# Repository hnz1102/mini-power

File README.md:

<div align="center">
  <h1><code>Mini Power for Breadboard</code></h1>
  
</div>

# Mini-Power

Mini-Power is a small, portable DC power supply unit designed to provide a convenient and reliable source of adjustable voltage for your electronic devices and breadboard experiments. Powered from a USB Power Delivery (PD) charger, it supports both Standard Power Range (SPR) and Extended Power Range (EPR) modes, making it perfect for electronics developers, students, and anyone who needs a compact bench power supply.

## Key Features

- **Easy access to the breadboard**: both sides accessible via standard 2.54mm pitch pin headers.
- **USB PD support**: 5V to 28V output using the AP33772S PD Sink Controller.
- **Variable voltage**: 0.1V steps using PPS APDO, with automatic fallback to the nearest Fixed PDO.
- **Real-time display**: SSD1306 128×64 OLED showing output voltage, measured voltage, current, power, WiFi status, and buffer usage.
- **Data logging**: Measurements sent to InfluxDB over WiFi (InfluxDB Line Protocol, HTTPS).
- **Remote syslog**: RFC 5424 over UDP for monitoring and troubleshooting.
- **HTTP web interface**: Real-time graphs (Chart.js), voltage control, and output ON/OFF toggle from any browser on the local network.
- **Three-button interface**: Up / Down / Center push buttons for direct voltage adjustment and output control.
- **NVS persistence**: Last voltage setting is saved to flash and restored on reboot.
- **Safety protections**: OVP, UVP, OCP (in AP33772S hardware) plus software current/power limits and voltage overshoot detection (>110% of setpoint).

## Hardware Components

| Reference | Part | Description |
|---|---|---|
| U103 | ESP32-C3-WROOM-02-N4 | Main microcontroller (RISC-V, built-in WiFi, 4MB flash) |
| U104 | AP33772SDKZ-13-FA01 | USB Power Delivery Sink Controller (SPR + EPR), QFN4040-24 |
| U102 | SSD1306 | Monochrome OLED display (128×64 pixels, I2C) |
| U101 | PCA9306D | Dual bidirectional I2C voltage-level translator (SSOP-8) |
| U105 | NJW1933F1 | Synchronous step-down DC/DC converter for 3.3V supply (SOT-23-6) |
| Q101, Q102 | DMN3008SFG | Dual N-channel MOSFET for output switching (PowerDI3333-8) |
| J101 | USB4105-GF-A | USB Type-C connector (input) |
| J102, J103 | 2×2 pin header | Output terminals (UPPER OUT / LOWER OUT), 2.54mm pitch |
| SW101–SW103 | TS-06104 | Push buttons: Up (GPIO10), Down (GPIO20), Center (GPIO21) |
| R110 | 5mΩ shunt resistor | Current sensing resistor (2512 package) |
| L101 | 22µH | Inductor for DC/DC converter |
| D101 | LED (Blue) | Status indicator |
| D102 | SK36A-LTP | Schottky diode (SMA) |
| FB101 | MH2029-601Y | Ferrite bead for EMI filtering |

Schematic and PCB files are in the `hardware/` directory. The board is designed with [KiCad](https://www.kicad.org/). A PDF export of the schematic is available at [`hardware/schematic.pdf`](hardware/schematic.pdf).

The [ap33772s-driver](https://github.com/hnz1102/ap33772s-driver) crate is used for all USB-PD communication with the AP33772S controller.

## Software Architecture

The firmware is written entirely in Rust using the ESP-IDF framework.

| File | Responsibility |
|---|---|
| `main.rs` | Startup, peripheral init, NVS load/save, main control loop |
| `usbpd.rs` | AP33772S PD driver wrapper (PDO negotiation, custom voltage request, VOUT control) |
| `displayctl.rs` | SSD1306 OLED driver, display thread, PDO list screen |
| `currentlogs.rs` | In-memory ring buffer (up to 127 records) for voltage/current/power/temp data |
| `transfer.rs` | InfluxDB Line Protocol HTTP transfer thread |
| `httpserver.rs` | HTTP server, REST API (`/api/status`, `/api/voltage`, `/api/output`, `/api/pdos`), embedded HTML/JS |
| `keyevent.rs` | GPIO key scanner (10ms polling, 100ms guard time) with long-press detection |
| `wifi.rs` | WiFi connection, RSSI monitoring, automatic reconnect |
| `syslogger.rs` | RFC 5424 UDP syslog, replaces the default ESP console logger |

## How to Use the Unit

### Basic Operation

1. **Connection**: Connect a USB-C PD charger*1 to the input port.
2. **Power On**: The unit negotiates PD profiles and scrolls through the available PDO list on the display.
3. **Main Screen**: After getting a IP address from DHCP server*2, the display shows output voltage, current, power, WiFi RSSI, IP address(last two octets)and buffer usage. 
4. **Voltage Selection**: Press **Up(yellow)** or **Down(blue)** to increase/decrease the target voltage in 0.1V steps.
5. **Output Control**: Press **Center(red)** to toggle output ON/OFF.
6. **Monitoring**: View real-time measurements on the OLED display or open `http://<device-ip>/` in a browser.

**Note** 
*1: When it doesn't connect to the PD charger, the display will show "No PD Power". Click the up/down buttons to show main screen. It only can output 5V.
*2: If it can't connect to WiFi, the display will show the main screen after 30 seconds, but without IP address and RSSI. 

### Button Controls

| Button | GPIO | Function |
|---|---|---|
| Up | GPIO10 | Increase output voltage by 0.1V |
| Down | GPIO20 | Decrease output voltage by 0.1V |
| Center | GPIO21 | Toggle output ON/OFF |

### OLED Display

The SSD1306 128×64 monochrome OLED display is divided into several regions as shown below.

| Area | Content | Detail |
|---|---|---|
| `V:xx.xV` | Measured voltage | Read from AP33772S (updated every 100ms when output ON) |
| `I:xx.xA` | Measured current | Read from AP33772S (updated every 100ms when output ON) |
| `SET:xx.xV` | Target output voltage | Blinks while PD voltage negotiation is in progress |
| `P:xx.xW` / `P:xx.xmW` | Measured power | Auto-range: switches between mW and W (threshold 0.5W / 1.0W) |
| `OUTPUT` / `STOPPED` | Output state | `OUTPUT` shown inverted (white on black) when output is ON |
| IP address | Last two octets of device IP | e.g. `IP:2.142` for `192.168.2.142` |
| Buffer bar | InfluxDB send buffer usage | 60px wide bar; fills left-to-right as records accumulate (max 127) |
| `xxx%` | Buffer usage percentage | Displayed to the right of the buffer bar |
| WiFi icon | WiFi signal strength | 5-level icon (wifi-0 to wifi-4) based on RSSI; animated while connecting |
| `+xx dBm` | RSSI value | Shown below WiFi icon when connected |
| Voltage bar (right edge) | PDO voltage range | Vertical bar showing min–max PD voltage; Variable/PPS range filled, Fixed PDO voltages marked as horizontal lines; current SET voltage shown as a longer line marker |

**Startup sequence:**

1. At boot, the PDO list screen is shown first — all Power Data Objects negotiated with the charger are listed (voltage, current, max power, type). Each page is shown for 3 seconds.
2. After PDO display completes, the main screen appears.
3. Error / warning messages (e.g. `Voltage Overshoot`, `Current OV x.xxxA`) replace the main screen temporarily and auto-dismiss after 3 seconds.

### HTTP Web Interface

When connected to WiFi, open `http://<device-ip>/` (IP shown on OLED display) to access:

- Live voltage, current, and power readings updated every second
- Real-time voltage and current graph (Chart.js)
- PDO table showing all available power profiles from the charger
- Voltage control with +/− buttons (0.1V step)
- Output ON/OFF toggle

### Safety Protections

| Protection | Mechanism |
|---|---|
| Over Voltage Protection (OVP) | AP33772S hardware |
| Under Voltage Protection (UVP) | AP33772S hardware |
| Over Current Protection (OCP) | AP33772S hardware |
| Software current limit | Output disabled if current exceeds `max_current_limit` |
| Software power limit | Output disabled if power exceeds `max_power_limit` |
| Voltage overshoot detection | Output disabled if measured voltage > 110% of setpoint |

## How to Build from Code and Install to the Unit

### Using Ubuntu 22.04 LTS

**1. Install Rust Compiler**

```bash
sudo apt update && sudo apt -y install git python3 python3-pip gcc build-essential \
  curl pkg-config libudev-dev libtinfo5 clang libclang-dev llvm-dev udev libssl-dev python3.10-venv nano
```
```bash
curl --proto '=https' --tlsv1.2 -sSf https://sh.rustup.rs | sh
# Select option 1 (default install)
```
```bash
source "$HOME/.cargo/env"
```

**2. Install toolchain for ESP32-C3**

```bash
cargo install ldproxy
cargo install cargo-binstall
cargo install espup
espup install
espup update
. ./export-esp.sh
cargo binstall cargo-espflash
```

**3. Add UDEV rules**

```bash
sudo sh -c 'echo "SUBSYSTEMS==\"usb\", ATTRS{idVendor}==\"303a\", ATTRS{idProduct}==\"1001\", MODE=\"0666\"" \
  > /etc/udev/rules.d/99-esp32.rules'
sudo udevadm control --reload-rules
sudo udevadm trigger
```

**4. Clone the repository**

```bash
git clone https://github.com/hnz1102/mini-power.git
cd mini-power/code
```

**5. Configure WiFi and InfluxDB**

```bash
cp cfg.toml.samp cfg.toml
nano cfg.toml
```

```toml
[mini-power]
wifi_ssid = "YOUR_WIFI_SSID"
wifi_psk = "YOUR_WIFI_PASSWORD"
influxdb_server = "192.168.x.x:8086"
influxdb_api_key = "<YOUR_API_KEY>"
influxdb_api = "/api/v2/write?org=<ORG>&bucket=LOGGER&precision=ns"
influxdb_measurement = "minipower"
influxdb_tag = "ch"
max_current_limit = "5.2"
max_power_limit = "100.0"
max_temperature = "75"
syslog_server = "192.168.x.x:514"
syslog_enable = "false"
```

**6. Connect the board and verify**

```bash
cargo espflash board-info
# Select /dev/ttyACM0
# Expected: Chip type: esp32c3, Flash size: 4MB
```

**7. Build and flash**

```bash
cargo espflash flash --release --monitor
```

The device boots automatically after flashing. The OLED display will show the PDO list negotiated with the charger, then switch to the main monitoring screen.

## How to Install InfluxDB and Configure the Dashboard

**1. Download and install InfluxDB**

```bash
wget https://dl.influxdata.com/influxdb/releases/influxdb2-2.7.0-amd64.deb
sudo dpkg -i influxdb2-2.7.0-amd64.deb
sudo service influxdb start
```

**2. Initial configuration**

Open `http://<server-ip>:8086`. Click `GET STARTED` and set:

| Term | Value |
|---|---|
| Username | Admin login username |
| Password | Admin login password |
| Initial Organization Name | e.g. `ORG` |
| Initial Bucket Name | `LOGGER` |

**3. Get the API Token**

Copy the Operator API Token shown after setup — you will not see it again. To generate a new token later: `API Tokens` → `GENERATE API TOKEN` → `All access token`.

**4. Import the Dashboard Template**

Click `Dashboard` → `CREATE DASHBOARD` → `Import Dashboard`. Drop the `influxdb/mimi-power.json` file into the import dialog, then click `IMPORT JSON AS DASHBOARD`.

You will see the **Mimi-POWER** dashboard. It contains three time-series graphs:

| Chart | Field | Unit |
|---|---|---|
| Voltage | `voltage` | V |
| Current | `current` | A |
| Power | `power` | W |

All charts query the `LOGGER` bucket, measurement `minipower`, tag `tag = "ch"`.

**5. Start logging**

Enable the output on the Mini-Power unit (Center button or web interface). Measurement data will be sent to InfluxDB and appear on the dashboard in real-time.

## Schematic and PCB Data

The PCB is designed with [KiCad](https://www.kicad.org/). All hardware design files are in the `hardware/` directory.

| File / Directory | Description |
|---|---|
| [`hardware/schematic.pdf`](hardware/schematic.pdf) | Schematic PDF (for viewing without KiCad) |
| `hardware/mini-power.kicad_sch` | KiCad schematic source |
| `hardware/mini-power.kicad_pcb` | KiCad PCB layout |
| `hardware/bom.csv` | Bill of Materials |
| `hardware/production/` | Gerber files for PCB manufacturing (`mini-power.kicad_pcb_gerber.zip`) |

## 3D Printed Enclosure

The enclosure design files are in the `hardware/Container/` directory.

| File | Description |
|---|---|
| `body.3mf` | Main enclosure body |
| `upper.3mf` | Top cover |
| `button.3mf` | Button cap for the three push switches |
| `mini-power.f3d` | Fusion 360 source file |

All parts are designed for FDM 3D printing. Print `body.3mf`, `upper.3mf`, and three copies of `button.3mf`.

## License

This source code is licensed under MIT. Other Hardware Schematic documents are licensed under CC-BY-SA V4.0.

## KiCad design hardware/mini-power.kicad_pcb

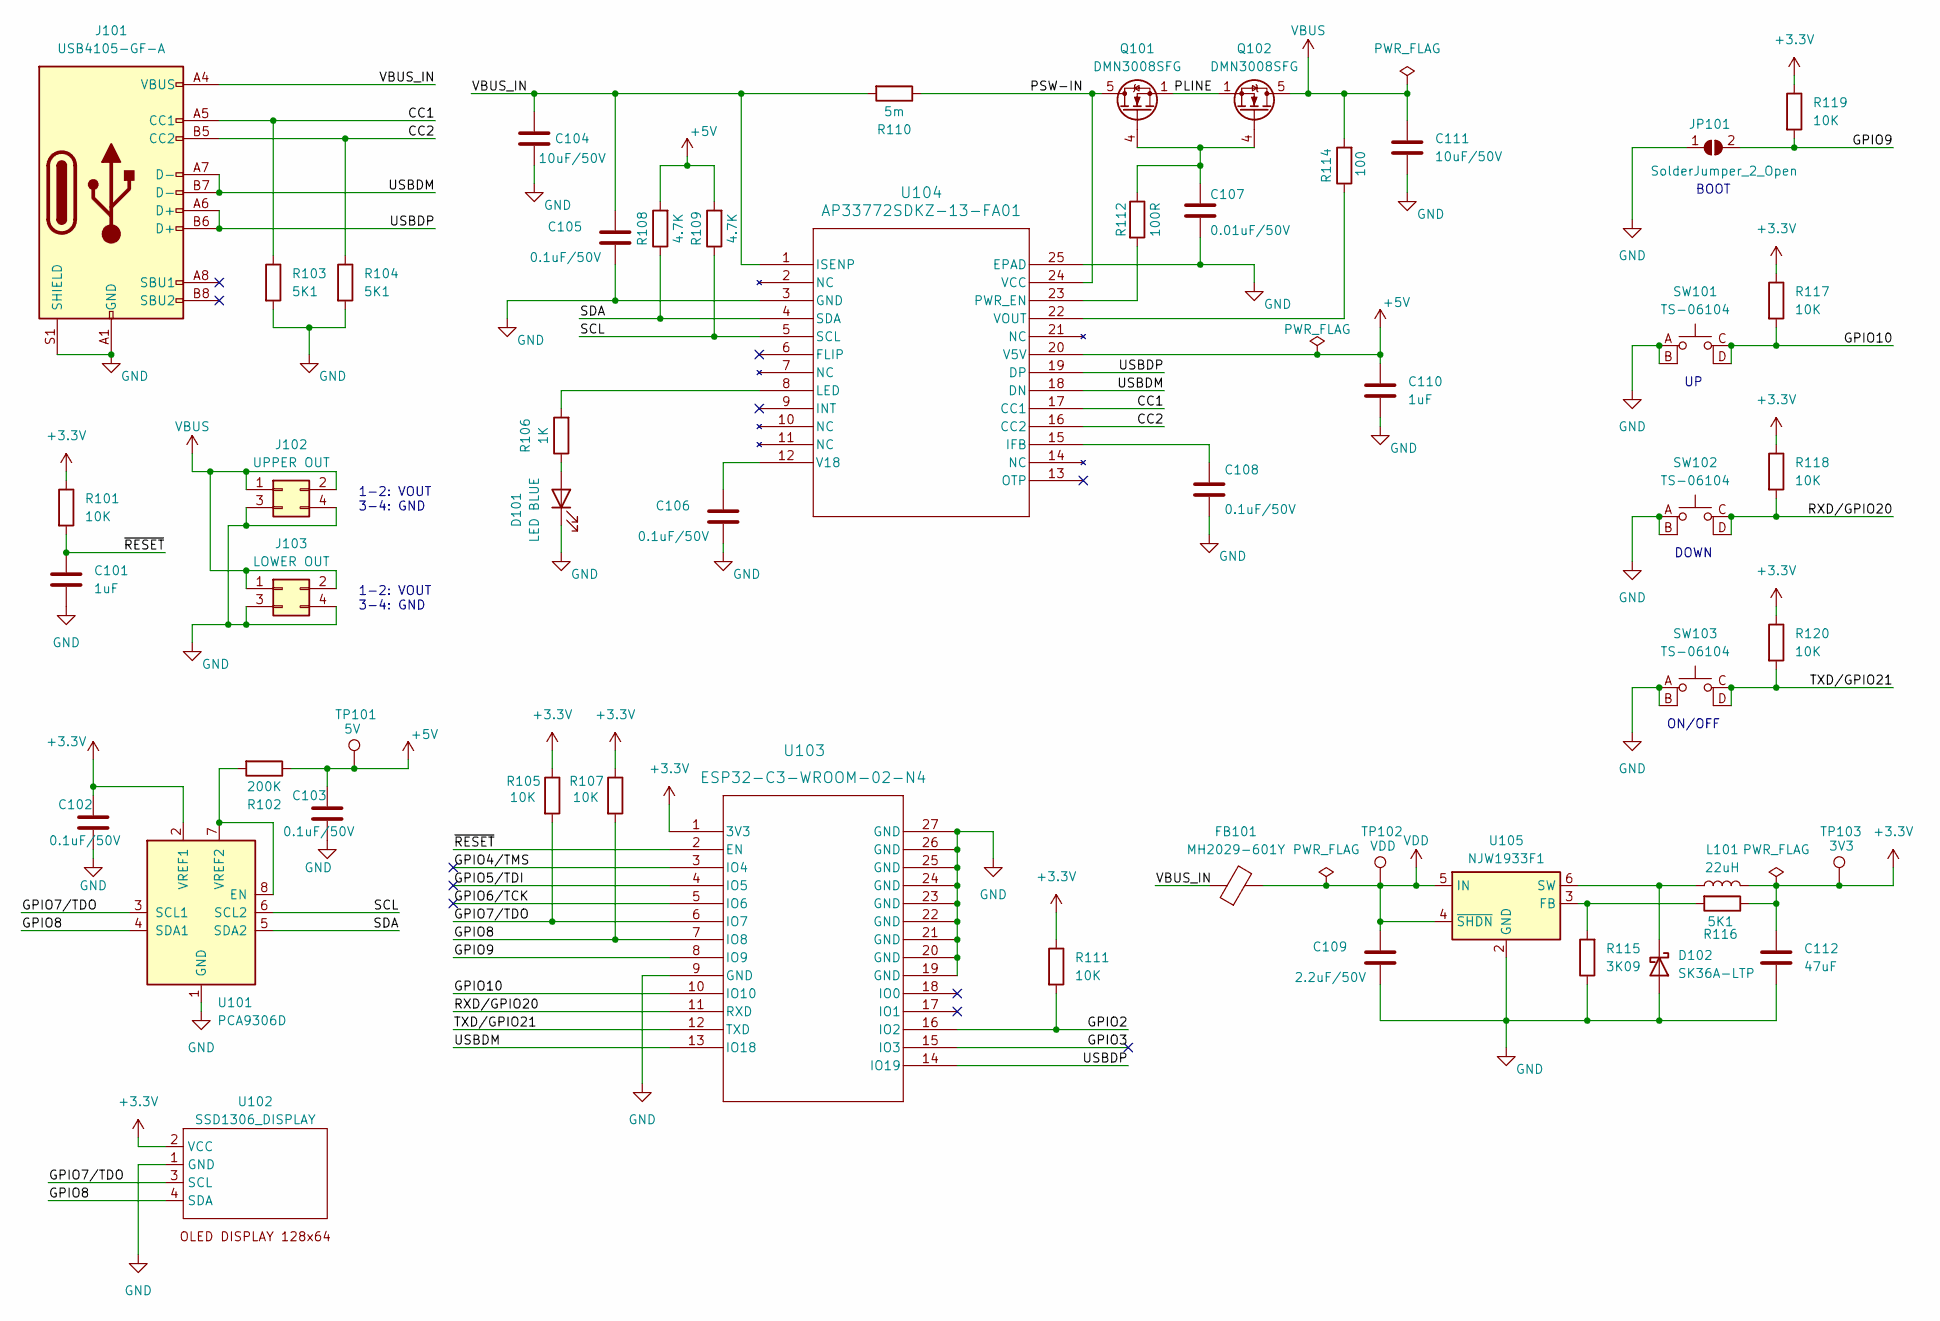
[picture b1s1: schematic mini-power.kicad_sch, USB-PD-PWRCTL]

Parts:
C101, C110: 1uF; C_0805_2012Metric; digikey 311-1365-1-ND
C102, C103, C105, C106, C108: 0.1uF/50V; C_0603_1608Metric; digikey 311-1343-1-ND
C104, C111: 10uF/50V; C_0805_2012Metric; digikey 490-18663-1-ND
C107: 0.01uF/50V; C_0603_1608Metric; digikey 311-1349-1-ND
C109: 2.2uF/50V; C_0603_1608Metric; digikey 587-4320-1-ND
C112: 47uF; C_0805_2012Metric; digikey 587-4280-1-ND
D101: LED BLUE; LED_0603_1608Metric; digikey 3147-B1931NB--20C007614U1930CT-ND
D102: SK36A-LTP; D_SMA; digikey SK36A-LTPMSCT-ND
FB101: MH2029-601Y; L_0805_2012Metric; digikey MH2029-601YCT-ND
J101: USB4105-GF-A; USB_C_5077CR-16-SMC2-BK-TR; digikey 2073-USB4105-GF-ACT-ND
J102: UPPER OUT; PinHeader_2x02_P2.54mm_Vertical; digikey 2057-PH2-04-UA-ND
J103: LOWER OUT; PinHeader_2x02_P2.54mm_Vertical; digikey 2057-PH2-04-UA-ND
JP101: SolderJumper_2_Open; SolderJumper-2_P1.3mm_Open_RoundedPad1.0x1.5mm
L101: 22uH; L_CHPH4D19FNP; digikey 308-1313-1-ND
Q101, Q102: DMN3008SFG; Diodes_PowerDI3333-8; digikey DMN3008SFG-7DICT-ND
R101, R105, R107, R111, R117, R118, R119, R120: 10K; R_0603_1608Metric; digikey 311-10.0KHRCT-ND
R102: 200K; R_0603_1608Metric; digikey 311-200KHRCT-ND
R103, R104, R116: 5K1; R_0603_1608Metric; digikey 311-5.10KHRCT-ND
R106: 1K; R_0603_1608Metric; digikey RMCF0603FT1K00CT-ND
R108, R109: 4.7K; R_0603_1608Metric; digikey 311-4.70KHRCT-ND
R110: 5m; R_2512_6332Metric_Pad1.40x3.35mm_HandSolder; digikey 4506-PEWF2512D5L00Q9CT-ND
R112: 100R; R_0603_1608Metric; digikey 311-10.0HRCT-ND
R114: 100; R_0603_1608Metric; digikey 311-100GRCT-ND
R115: 3K09; R_0603_1608Metric; digikey 311-3.09KHRCT-ND
SW101, SW102, SW103: TS-06104; digikey C2939203 JLPCB Part#
TP101: 5V; TestPoint_Pad_D1.0mm
TP102: VDD; TestPoint_Pad_D1.0mm
TP103: 3V3; TestPoint_Pad_D1.0mm
U101: PCA9306D; SSOP-8_2.95x2.8mm_P0.65mm; digikey 568-4215-1-ND
U102: SSD1306_DISPLAY; OLED I2C DISPLAY
U103: ESP32-C3-WROOM-02-N4; IC18_ESP32-C3-WROOM-02-N4_EXP; digikey 1965-ESP32-C3-WROOM-02-N4CT-ND
U104: AP33772SDKZ-13-FA01; W-QFN4040-24_Type_A1_DIO; digikey 31-AP33772SDKZ-13-FA01CT-ND
U105: NJW1933F1; SOT-23-6

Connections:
+3.3V: C102.1, C112.1, L101.2, R101.1, R105.1, R107.1, R111.1, R116.1, R117.1, R118.1, R119.1, R120.1, TP103.1, U101.2 (VREF1), U102.2 (VCC), U103.1 (3V3)
+5V: C103.1, C110.1, R102.1, R108.2, R109.2, TP101.1, U104.20 (V5V)
/CC1: J101.A5 (CC1), R103.1, U104.17 (CC1)
/CC2: J101.B5 (CC2), R104.1, U104.16 (CC2)
/GPIO2: R111.2, U103.16 (IO2)
/GPIO3: U103.15 (IO3)
/GPIO4/TMS: U103.3 (IO4)
/GPIO5/TDI: U103.4 (IO5)
/GPIO6/TCK: U103.5 (IO6)
/GPIO7/TDO: R105.2, U101.3 (SCL1), U102.3 (SCL), U103.6 (IO7)
/GPIO8: R107.2, U101.4 (SDA1), U102.4 (SDA), U103.7 (IO8)
/GPIO9: JP101.2 (B), R119.2, U103.8 (IO9)
/GPIO10: R117.2, SW101.C, SW101.D, U103.10 (IO10)
/PLINE: Q101.1 (S), Q101.2 (S), Q101.3 (S), Q102.1 (S), Q102.2 (S), Q102.3 (S)
/PSW-IN: Q101.5 (D), R110.1, U104.24 (VCC)
/RXD/GPIO20: R118.2, SW102.C, SW102.D, U103.11 (RXD)
/SCL: R109.1, U101.6 (SCL2), U104.5 (SCL)
/SDA: R108.1, U101.5 (SDA2), U104.4 (SDA)
/TXD/GPIO21: R120.2, SW103.C, SW103.D, U103.12 (TXD)
/USBDM: J101.A7 (D-), J101.B7 (D-), U103.13 (IO18), U104.18 (DN)
/USBDP: J101.A6 (D+), J101.B6 (D+), U103.14 (IO19), U104.19 (DP)
/VBUS_IN: C104.1, C105.1, FB101.1, J101.A4 (VBUS), J101.A9 (VBUS), J101.B4 (VBUS), J101.B9 (VBUS), R110.2, U104.1 (ISENP)
/~RESET: C101.1, R101.2, U103.2 (EN)
GND: C101.2, C102.2, C103.2, C104.2, C105.2, C106.2, C107.2, C108.2, C109.2, C110.2, C111.2, C112.2, D101.1 (K), D102.2 (A), J101.A1 (GND), J101.A12 (GND), J101.B1 (GND), J101.B12 (GND), J101.S1 (SHIELD), J102.3, J102.4, J103.3, J103.4, JP101.1 (A), R103.2, R104.2, R115.1, SW101.A, SW101.B, SW102.A, SW102.B, SW103.A, SW103.B, U101.1 (GND), U102.1 (GND), U103.9 (GND), U103.19 (GND), U103.20 (GND), U103.21 (GND), U103.22 (GND), U103.23 (GND), U103.24 (GND), U103.25 (GND), U103.26 (GND), U103.27 (GND), U104.3 (GND), U104.25 (EPAD), U105.2 (GND)
unnamed: D101.2 (A), R106.1
unnamed: D102.1 (K), L101.1, U105.6 (SW)
unnamed: C107.1, Q101.4 (G), Q102.4 (G), R112.1
unnamed: R102.2, U101.7 (VREF2), U101.8 (EN)
unnamed: C108.1, U104.15 (IFB)
unnamed: R106.2, U104.8 (LED)
unnamed: R112.2, U104.23 (PWR_EN)
unnamed: C106.1, U104.12 (V18)
unnamed: R114.1, U104.22 (VOUT)
unnamed: R115.2, R116.2, U105.3 (FB)
VBUS: C111.1, J102.1, J102.2, J103.1, J103.2, Q102.5 (D), R114.2
VDD: C109.1, FB101.2, TP102.1, U105.4 (~SHDN), U105.5 (IN)

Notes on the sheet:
DOWN
1-2: VOUT 3-4: GND
ON/OFF
BOOT

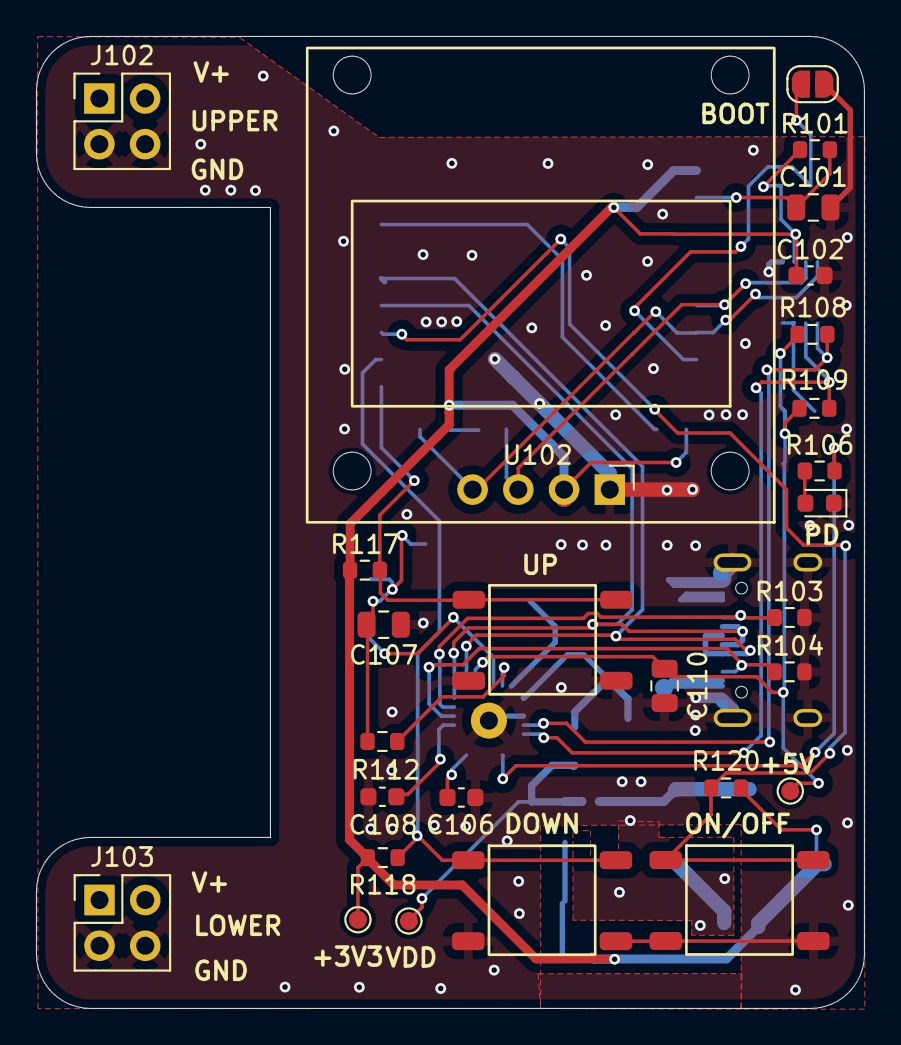
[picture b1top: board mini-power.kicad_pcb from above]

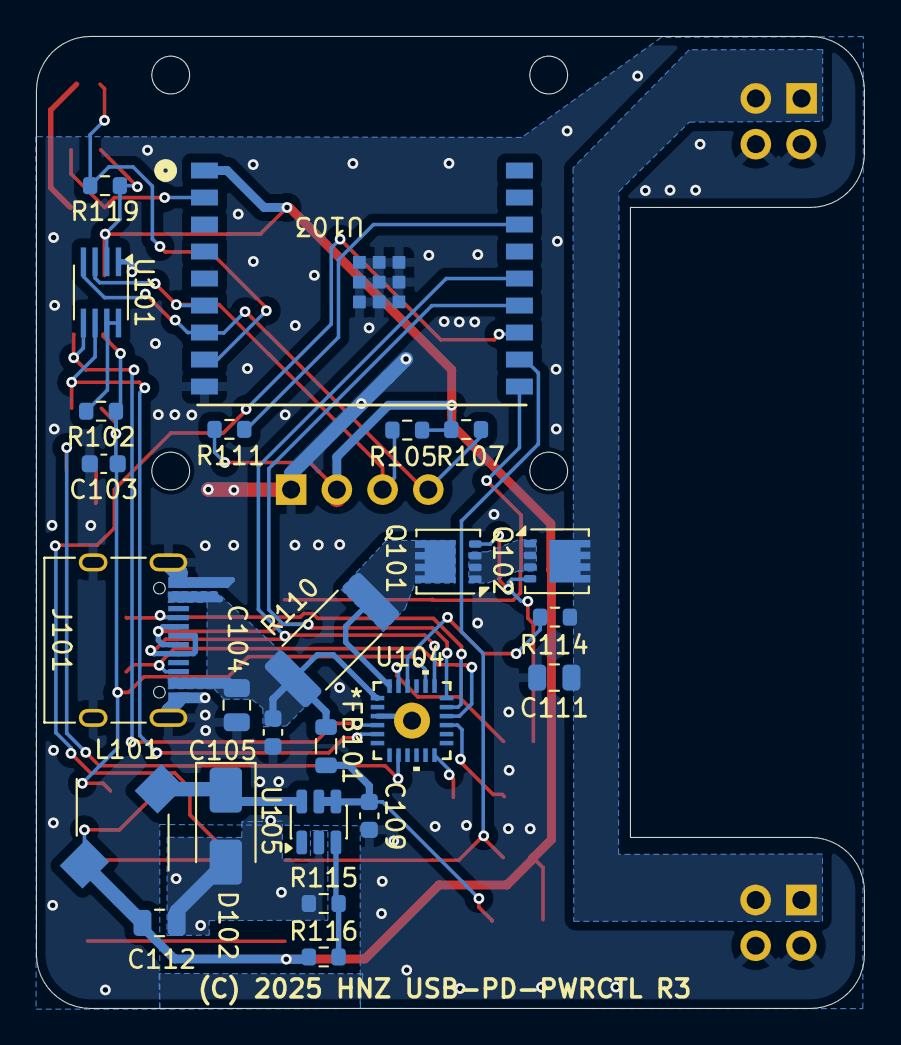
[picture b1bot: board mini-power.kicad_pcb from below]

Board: 2 copper layers, 46.0 x 54.0 mm, 52 parts (25 on the bottom side), 32 nets.

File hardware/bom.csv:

Reference	Qty	Value	DNP	Exclude from BOM	Exclude from Board	Footprint	Datasheet	digikey
C101,C110	2	1uF				Capacitor_SMD:C_0805_2012Metric	~	311-1365-1-ND
C102,C103,C105,C106,C108	5	0.1uF/50V				Capacitor_SMD:C_0603_1608Metric	~	311-1343-1-ND
C104,C111	2	10uF/50V				Capacitor_SMD:C_0805_2012Metric	~	490-18663-1-ND
C107	1	0.01uF/50V				Capacitor_SMD:C_0603_1608Metric	~	311-1349-1-ND
C109	1	2.2uF/50V				Capacitor_SMD:C_0603_1608Metric	~	587-4320-1-ND
C112	1	47uF				Capacitor_SMD:C_0805_2012Metric	~	587-4280-1-ND
D101	1	LED BLUE				LED_SMD:LED_0603_1608Metric	~	3147-B1931NB--20C007614U1930CT-ND
D102	1	SK36A-LTP				Diode_SMD:D_SMA		SK36A-LTPMSCT-ND
FB101	1	MH2029-601Y				Inductor_SMD:L_0805_2012Metric	~	MH2029-601YCT-ND
J101	1	USB4105-GF-A				Library:USB_C_5077CR-16-SMC2-BK-TR	https://www.usb.org/sites/default/files/documents/usb_type-c.zip	2073-USB4105-GF-ACT-ND
J102	1	UPPER OUT				Connector_PinHeader_2.54mm:PinHeader_2x02_P2.54mm_Vertical	~	2057-PH2-04-UA-ND
J103	1	LOWER OUT				Connector_PinHeader_2.54mm:PinHeader_2x02_P2.54mm_Vertical	~	2057-PH2-04-UA-ND
JP101	1	SolderJumper_2_Open				Jumper:SolderJumper-2_P1.3mm_Open_RoundedPad1.0x1.5mm	~	-
L101	1	22uH				Library:L_CHPH4D19FNP	~	308-1313-1-ND
Q101,Q102	2	DMN3008SFG				Package_SON:Diodes_PowerDI3333-8	https://www.diodes.com/assets/Datasheets/DMN3008SFG.pdf	DMN3008SFG-7DICT-ND
R101,R105,R107,R111,R117,R118,R119,R120	8	10K				Resistor_SMD:R_0603_1608Metric	~	311-10.0KHRCT-ND
R102	1	200K				Resistor_SMD:R_0603_1608Metric	~	311-200KHRCT-ND
R103,R104,R116	3	5K1				Resistor_SMD:R_0603_1608Metric	~	311-5.10KHRCT-ND
R106	1	1K				Resistor_SMD:R_0603_1608Metric	~	RMCF0603FT1K00CT-ND
R108,R109	2	4.7K				Resistor_SMD:R_0603_1608Metric	~	311-4.70KHRCT-ND
R110	1	5m				Resistor_SMD:R_2512_6332Metric_Pad1.40x3.35mm_HandSolder	~	4506-PEWF2512D5L00Q9CT-ND 
R112	1	100R				Resistor_SMD:R_0603_1608Metric	~	311-10.0HRCT-ND
R114	1	100				Resistor_SMD:R_0603_1608Metric	~	311-100GRCT-ND
R115	1	3K09				Resistor_SMD:R_0603_1608Metric	~	311-3.09KHRCT-ND
SW101,SW102,SW103	3	TS-06104				Library:TS-06104		C2939203 JLPCB Part#
TP101	1	5V				TestPoint:TestPoint_Pad_D1.0mm	~	-
TP102	1	VDD				TestPoint:TestPoint_Pad_D1.0mm	~	-
TP103	1	3V3				TestPoint:TestPoint_Pad_D1.0mm	~	-
U101	1	PCA9306D				Package_SO:SSOP-8_2.95x2.8mm_P0.65mm	https://www.nxp.com/docs/en/data-sheet/PCA9306.pdf	568-4215-1-ND
U102	1	SSD1306_DISPLAY				Library:OLED I2C DISPLAY		https://akizukidenshi.com/catalog/g/g112031/
U103	1	ESP32-C3-WROOM-02-N4				Library:IC18_ESP32-C3-WROOM-02-N4_EXP	ESP32-C3-WROOM-02-N4	1965-ESP32-C3-WROOM-02-N4CT-ND
U104	1	AP33772SDKZ-13-FA01				Library:W-QFN4040-24_Type_A1_DIO	AP33772SDKZ-13	31-AP33772SDKZ-13-FA01CT-ND
U105	1	NJW1933F1				Package_TO_SOT_SMD:SOT-23-6

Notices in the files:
hardware/mini-power.kicad_pcb:
(C) 2025 HNZ USB-PD-PWRCTL R3
hardware/mini-power.kicad_sch:
(C) 2025 Hiroshi Nakajima
